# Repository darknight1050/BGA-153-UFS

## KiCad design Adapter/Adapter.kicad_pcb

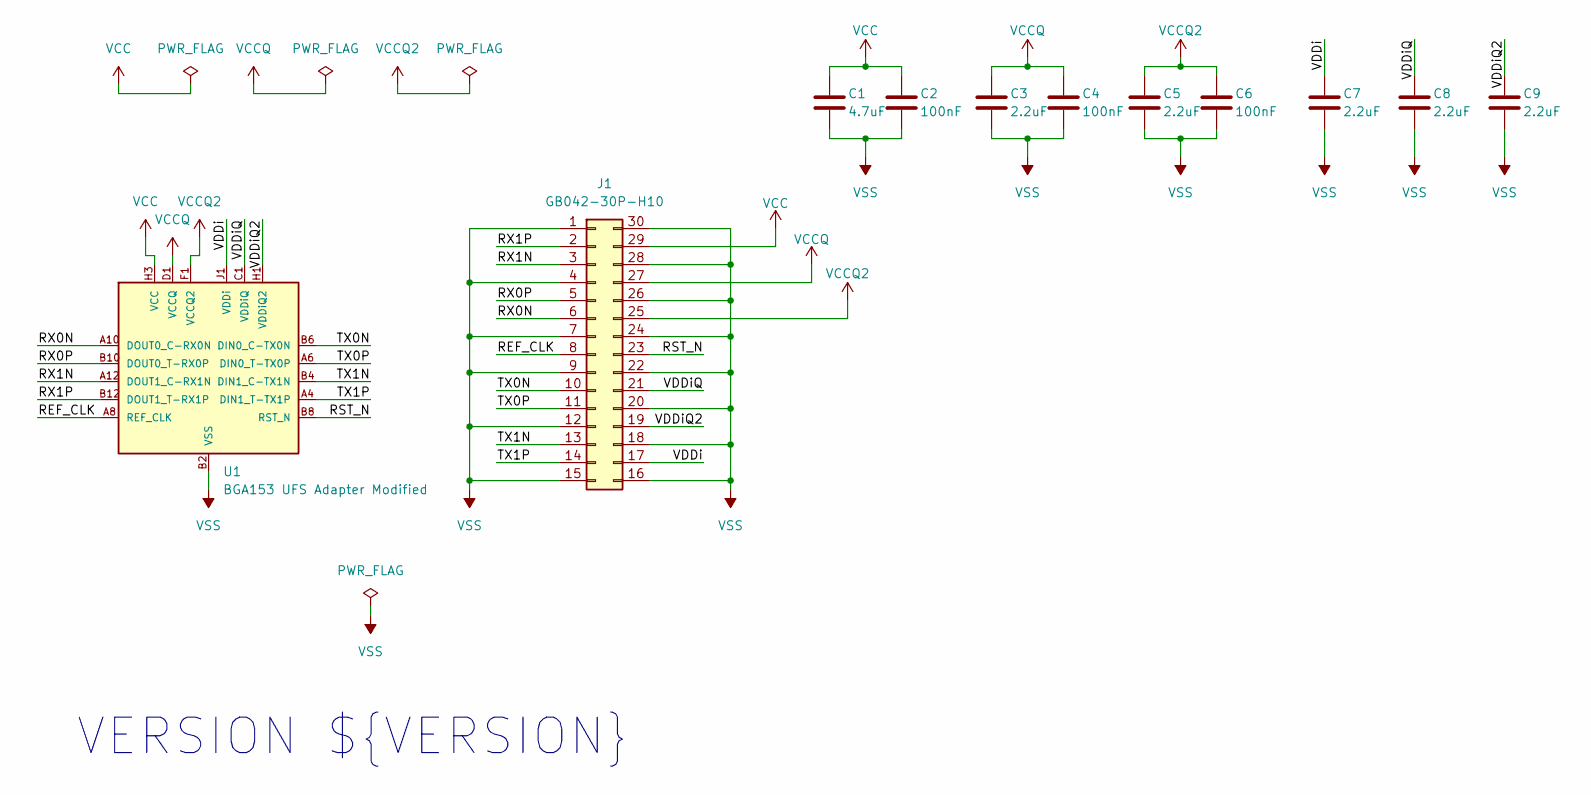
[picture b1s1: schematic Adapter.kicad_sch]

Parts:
C1: 4.7uF; C_0402_1005Metric_Pad0.74x0.62mm_HandSolder
C2, C4, C6: 100nF; C_0402_1005Metric_Pad0.74x0.62mm_HandSolder
C3, C5, C7, C8, C9: 2.2uF; C_0402_1005Metric_Pad0.74x0.62mm_HandSolder
J1: GB042-30P-H10
U1: BGA153 UFS Adapter Modified; BGA 153 Adapter Modified

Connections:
/REF_CLK: J1.8, U1.A8 (REF_CLK)
/RST_N: J1.23, U1.B8 (RST_N)
/RX0N: J1.6, U1.A10 (DOUT0_C-RX0N)
/RX0P: J1.5, U1.B10 (DOUT0_T-RX0P)
/RX1N: J1.3, U1.A12 (DOUT1_C-RX1N)
/RX1P: J1.2, U1.B12 (DOUT1_T-RX1P)
/TX0N: J1.10, U1.B6 (DIN0_C-TX0N)
/TX0P: J1.11, U1.A6 (DIN0_T-TX0P)
/TX1N: J1.13, U1.B4 (DIN1_C-TX1N)
/TX1P: J1.14, U1.A4 (DIN1_T-TX1P)
/VDDi: C7.1, J1.17, U1.J1 (VDDi)
/VDDiQ: C8.1, J1.21, U1.C1 (VDDiQ)
/VDDiQ2: C9.1, J1.19, U1.H1 (VDDiQ2)
VCC: C1.1, C2.1, J1.29, U1.H2 (VCC), U1.H3 (VCC), U1.H5 (VCC), U1.H10 (VCC), U1.H13 (VCC), U1.H14 (VCC), U1.J2 (VCC), U1.J3 (VCC), U1.J13 (VCC), U1.J14 (VCC)
VCCQ: C3.1, C4.1, J1.27, U1.D1 (VCCQ), U1.D2 (VCCQ), U1.D3 (VCCQ), U1.E1 (VCCQ), U1.E2 (VCCQ), U1.E3 (VCCQ), U1.E5 (VCCQ), U1.E6 (VCCQ)
VCCQ2: C5.1, C6.1, J1.25, U1.F1 (VCCQ2), U1.F2 (VCCQ2), U1.F3 (VCCQ2), U1.F10 (VCCQ2), U1.G1 (VCCQ2), U1.G2 (VCCQ2), U1.G3 (VCCQ2), U1.G10 (VCCQ2)
VSS: C1.2, C2.2, C3.2, C4.2, C5.2, C6.2, C7.2, C8.2, C9.2, J1.1, J1.4, J1.7, J1.9, J1.12, J1.15, J1.16, J1.18, J1.20, J1.22, J1.24, J1.26, J1.28, J1.30, U1.B2 (VSS), U1.B3 (VSS), U1.C3 (VSS), U1.C4 (VSS), U1.C5 (VSS), U1.C6 (VSS), U1.C7 (VSS), U1.C8 (VSS), U1.C9 (VSS), U1.C10 (VSS), U1.C11 (VSS), U1.C12 (VSS), U1.C13 (VSS), U1.D12 (VSS), U1.D13 (VSS), U1.D14 (VSS), U1.E8 (VSS), U1.E9 (VSS), U1.E10 (VSS), U1.E12 (VSS), U1.E13 (VSS), U1.E14 (VSS), U1.K7 (VSS), U1.K8 (VSS), U1.L2 (VSS), U1.L3 (VSS), U1.L13 (VSS), U1.L14 (VSS), U1.M2 (VSS), U1.M3 (VSS), U1.M4 (VSS), U1.M5 (VSS), U1.M6 (VSS), U1.M7 (VSS), U1.M8 (VSS), U1.M9 (VSS), U1.M10 (VSS), U1.M11 (VSS), U1.M12 (VSS), U1.M13 (VSS), U1.M14 (VSS), U1.N4 (VSS), U1.N6 (VSS), U1.N8 (VSS), U1.N10 (VSS), U1.N12 (VSS), U1.P4 (VSS), U1.P6 (VSS), U1.P8 (VSS), U1.P10 (VSS), U1.P12 (VSS)

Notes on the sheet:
VERSION ${VERSION}

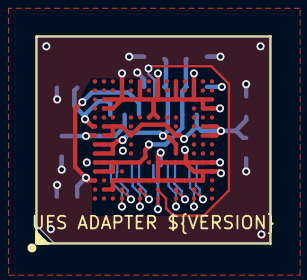
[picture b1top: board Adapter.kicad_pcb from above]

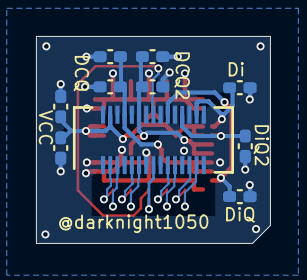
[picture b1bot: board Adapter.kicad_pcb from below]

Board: 4 copper layers, 13.0 x 11.5 mm, 11 parts (10 on the bottom side), 17 nets.

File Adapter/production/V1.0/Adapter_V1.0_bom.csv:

Designator,Footprint,Quantity,Value,LCSC Part #
C1,0402,1,4.7uF,
"C2, C4, C6",0402,3,100nF,
"C3, C5, C7, C8, C9",0402,5,2.2uF,
J2,FPC 14 Pin 0.5P,1,Conn_01x14_Socket,
U1,BGA 153 Modified,1,BGA153 UFS Modified,

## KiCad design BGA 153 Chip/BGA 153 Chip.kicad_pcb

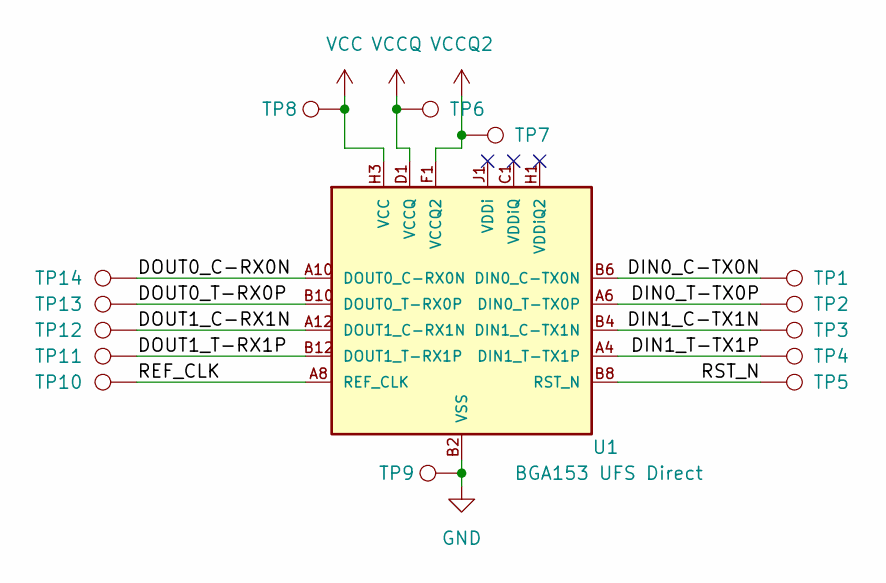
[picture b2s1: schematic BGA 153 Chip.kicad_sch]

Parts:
TP1, TP2, TP3, TP4, TP5, TP6, TP7, TP8, TP9, TP10, TP11, TP12, TP13, TP14: TestPoint; Pad
U1: BGA153 UFS Direct; BGA 153 Chip Direct

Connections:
/DIN0_C-TX0N: TP1.1, U1.B6 (DIN0_C-TX0N)
/DIN0_T-TX0P: TP2.1, U1.A6 (DIN0_T-TX0P)
/DIN1_C-TX1N: TP3.1, U1.B4 (DIN1_C-TX1N)
/DIN1_T-TX1P: TP4.1, U1.A4 (DIN1_T-TX1P)
/DOUT0_C-RX0N: TP14.1, U1.A10 (DOUT0_C-RX0N)
/DOUT0_T-RX0P: TP13.1, U1.B10 (DOUT0_T-RX0P)
/DOUT1_C-RX1N: TP12.1, U1.A12 (DOUT1_C-RX1N)
/DOUT1_T-RX1P: TP11.1, U1.B12 (DOUT1_T-RX1P)
/REF_CLK: TP10.1, U1.A8 (REF_CLK)
/RST_N: TP5.1, U1.B8 (RST_N)
GND: TP9.1, U1.B2 (VSS), U1.C3 (VSS), U1.C4 (VSS), U1.C5 (VSS), U1.C6 (VSS), U1.C7 (VSS), U1.C8 (VSS), U1.C9 (VSS), U1.C10 (VSS), U1.C11 (VSS), U1.C12 (VSS), U1.C13 (VSS), U1.D12 (VSS), U1.D13 (VSS), U1.D14 (VSS), U1.E8 (VSS), U1.E9 (VSS), U1.E10 (VSS), U1.E12 (VSS), U1.E13 (VSS), U1.E14 (VSS), U1.K7 (VSS), U1.K8 (VSS), U1.L2 (VSS), U1.L3 (VSS), U1.L13 (VSS), U1.L14 (VSS), U1.M2 (VSS), U1.M3 (VSS), U1.M4 (VSS), U1.M5 (VSS), U1.M6 (VSS), U1.M7 (VSS), U1.M8 (VSS), U1.M9 (VSS), U1.M10 (VSS), U1.M11 (VSS), U1.M12 (VSS), U1.M13 (VSS), U1.M14 (VSS), U1.N4 (VSS), U1.N6 (VSS), U1.N8 (VSS), U1.N10 (VSS), U1.N12 (VSS), U1.P4 (VSS), U1.P6 (VSS), U1.P8 (VSS), U1.P10 (VSS), U1.P12 (VSS)
VCC: TP8.1, U1.H2 (VCC), U1.H3 (VCC), U1.H5 (VCC), U1.H10 (VCC), U1.H13 (VCC), U1.H14 (VCC), U1.J2 (VCC), U1.J3 (VCC), U1.J13 (VCC), U1.J14 (VCC)
VCCQ: TP6.1, U1.D1 (VCCQ), U1.D2 (VCCQ), U1.D3 (VCCQ), U1.E1 (VCCQ), U1.E2 (VCCQ), U1.E3 (VCCQ), U1.E5 (VCCQ), U1.E6 (VCCQ)
VCCQ2: TP7.1, U1.F1 (VCCQ2), U1.F2 (VCCQ2), U1.F3 (VCCQ2), U1.F10 (VCCQ2), U1.G1 (VCCQ2), U1.G2 (VCCQ2), U1.G3 (VCCQ2), U1.G10 (VCCQ2)

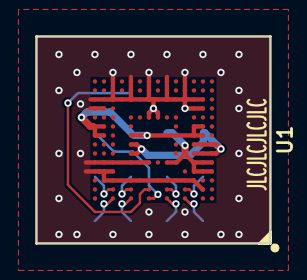
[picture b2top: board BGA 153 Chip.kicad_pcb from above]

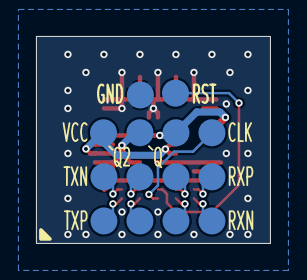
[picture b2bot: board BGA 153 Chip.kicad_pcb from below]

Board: 2 copper layers, 13.0 x 11.5 mm, 15 parts (14 on the bottom side), 14 nets.

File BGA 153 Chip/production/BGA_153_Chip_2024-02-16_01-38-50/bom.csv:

Designator,Footprint,Quantity,Value,LCSC Part #
"TP1, TP10, TP11, TP12, TP13, TP14, TP2, TP3, TP4, TP5, TP6, TP7, TP8, TP9",Pad,14,TestPoint,
U1,BGA 153 Chip Direct,1,BGA153 UFS Direct,

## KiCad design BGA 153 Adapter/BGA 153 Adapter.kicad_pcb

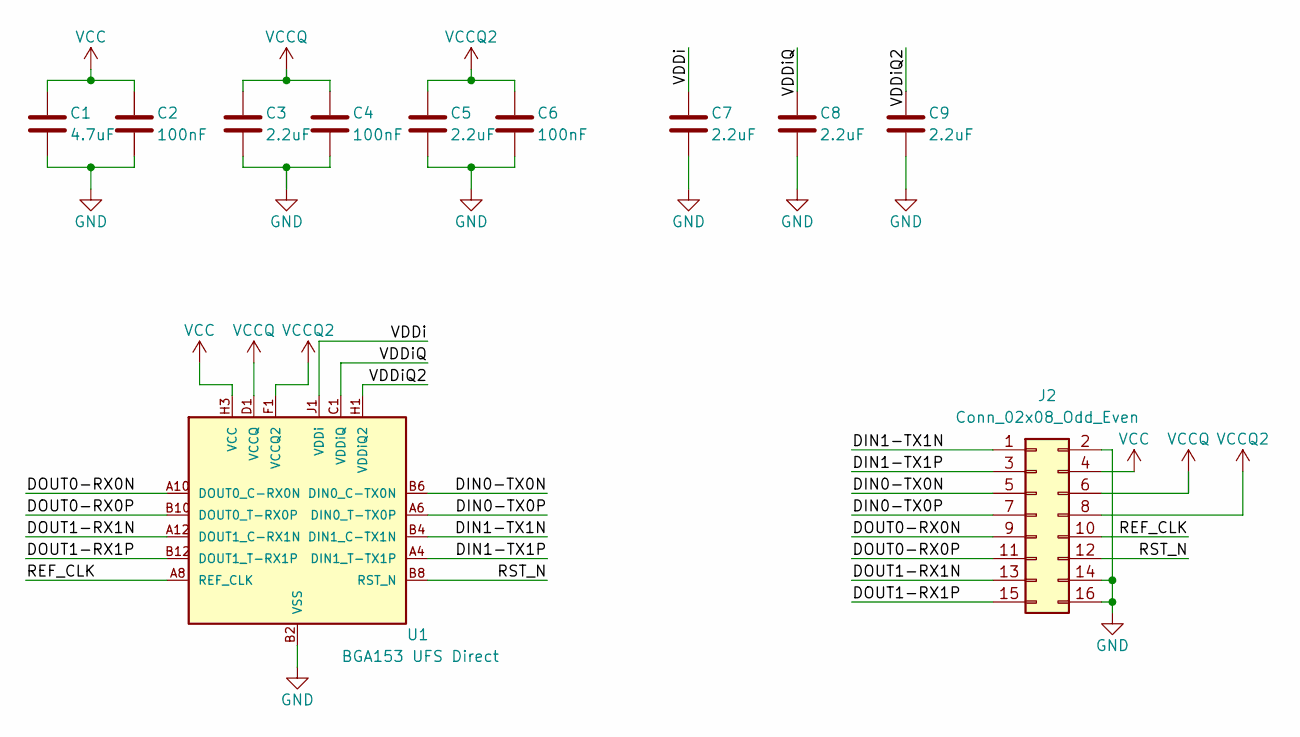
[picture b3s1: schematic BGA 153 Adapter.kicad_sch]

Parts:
C1: 4.7uF; C_0603_1608Metric
C2, C4, C6: 100nF; C_0603_1608Metric
C3, C5, C7, C8, C9: 2.2uF; C_0603_1608Metric
J2: Conn_02x08_Odd_Even; PinSocket_2x08_P2.54mm_Vertical
U1: BGA153 UFS Direct; BGA 153 Direct

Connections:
/DIN0-TX0N: J2.5, U1.B6 (DIN0_C-TX0N)
/DIN0-TX0P: J2.7, U1.A6 (DIN0_T-TX0P)
/DIN1-TX1N: J2.1, U1.B4 (DIN1_C-TX1N)
/DIN1-TX1P: J2.3, U1.A4 (DIN1_T-TX1P)
/DOUT0-RX0N: J2.9, U1.A10 (DOUT0_C-RX0N)
/DOUT0-RX0P: J2.11, U1.B10 (DOUT0_T-RX0P)
/DOUT1-RX1N: J2.13, U1.A12 (DOUT1_C-RX1N)
/DOUT1-RX1P: J2.15, U1.B12 (DOUT1_T-RX1P)
/REF_CLK: J2.10, U1.A8 (REF_CLK)
/RST_N: J2.12, U1.B8 (RST_N)
/VDDi: C7.1, U1.J1 (VDDi)
/VDDiQ: C8.1, U1.C1 (VDDiQ)
/VDDiQ2: C9.1, U1.H1 (VDDiQ2)
GND: C1.2, C2.2, C3.2, C4.2, C5.2, C6.2, C7.2, C8.2, C9.2, J2.2, J2.14, J2.16, U1.B2 (VSS), U1.C3 (VSS), U1.C4 (VSS), U1.C5 (VSS), U1.C6 (VSS), U1.C7 (VSS), U1.C8 (VSS), U1.C9 (VSS), U1.C10 (VSS), U1.C11 (VSS), U1.C12 (VSS), U1.C13 (VSS), U1.D12 (VSS), U1.D13 (VSS), U1.D14 (VSS), U1.E8 (VSS), U1.E9 (VSS), U1.E10 (VSS), U1.E12 (VSS), U1.E13 (VSS), U1.E14 (VSS), U1.K7 (VSS), U1.K8 (VSS), U1.L2 (VSS), U1.L3 (VSS), U1.L13 (VSS), U1.L14 (VSS), U1.M2 (VSS), U1.M3 (VSS), U1.M4 (VSS), U1.M5 (VSS), U1.M6 (VSS), U1.M7 (VSS), U1.M8 (VSS), U1.M9 (VSS), U1.M10 (VSS), U1.M11 (VSS), U1.M12 (VSS), U1.M13 (VSS), U1.M14 (VSS), U1.N4 (VSS), U1.N6 (VSS), U1.N8 (VSS), U1.N10 (VSS), U1.N12 (VSS), U1.P4 (VSS), U1.P6 (VSS), U1.P8 (VSS), U1.P10 (VSS), U1.P12 (VSS)
VCC: C1.1, C2.1, J2.4, U1.H2 (VCC), U1.H3 (VCC), U1.H5 (VCC), U1.H10 (VCC), U1.H13 (VCC), U1.H14 (VCC), U1.J2 (VCC), U1.J3 (VCC), U1.J13 (VCC), U1.J14 (VCC)
VCCQ: C3.1, C4.1, J2.6, U1.D1 (VCCQ), U1.D2 (VCCQ), U1.D3 (VCCQ), U1.E1 (VCCQ), U1.E2 (VCCQ), U1.E3 (VCCQ), U1.E5 (VCCQ), U1.E6 (VCCQ)
VCCQ2: C5.1, C6.1, J2.8, U1.F1 (VCCQ2), U1.F2 (VCCQ2), U1.F3 (VCCQ2), U1.F10 (VCCQ2), U1.G1 (VCCQ2), U1.G2 (VCCQ2), U1.G3 (VCCQ2), U1.G10 (VCCQ2)

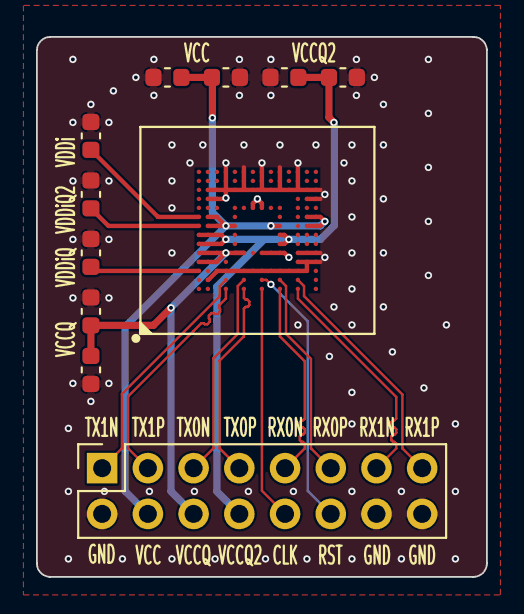
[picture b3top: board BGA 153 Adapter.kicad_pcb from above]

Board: 4 copper layers, 25.0 x 30.0 mm, 11 parts (0 on the bottom side), 17 nets.

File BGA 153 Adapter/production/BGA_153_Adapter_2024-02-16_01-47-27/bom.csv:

Designator,Footprint,Quantity,Value,LCSC Part #
C1,0603,1,4.7uF,
"C2, C4, C6",0603,3,100nF,
"C3, C5, C7, C8, C9",0603,5,2.2uF,
J2,PinSocket_2x08_P2.54mm_Vertical,1,Conn_02x08_Odd_Even,
U1,BGA 153 Direct,1,BGA153 UFS Direct,
